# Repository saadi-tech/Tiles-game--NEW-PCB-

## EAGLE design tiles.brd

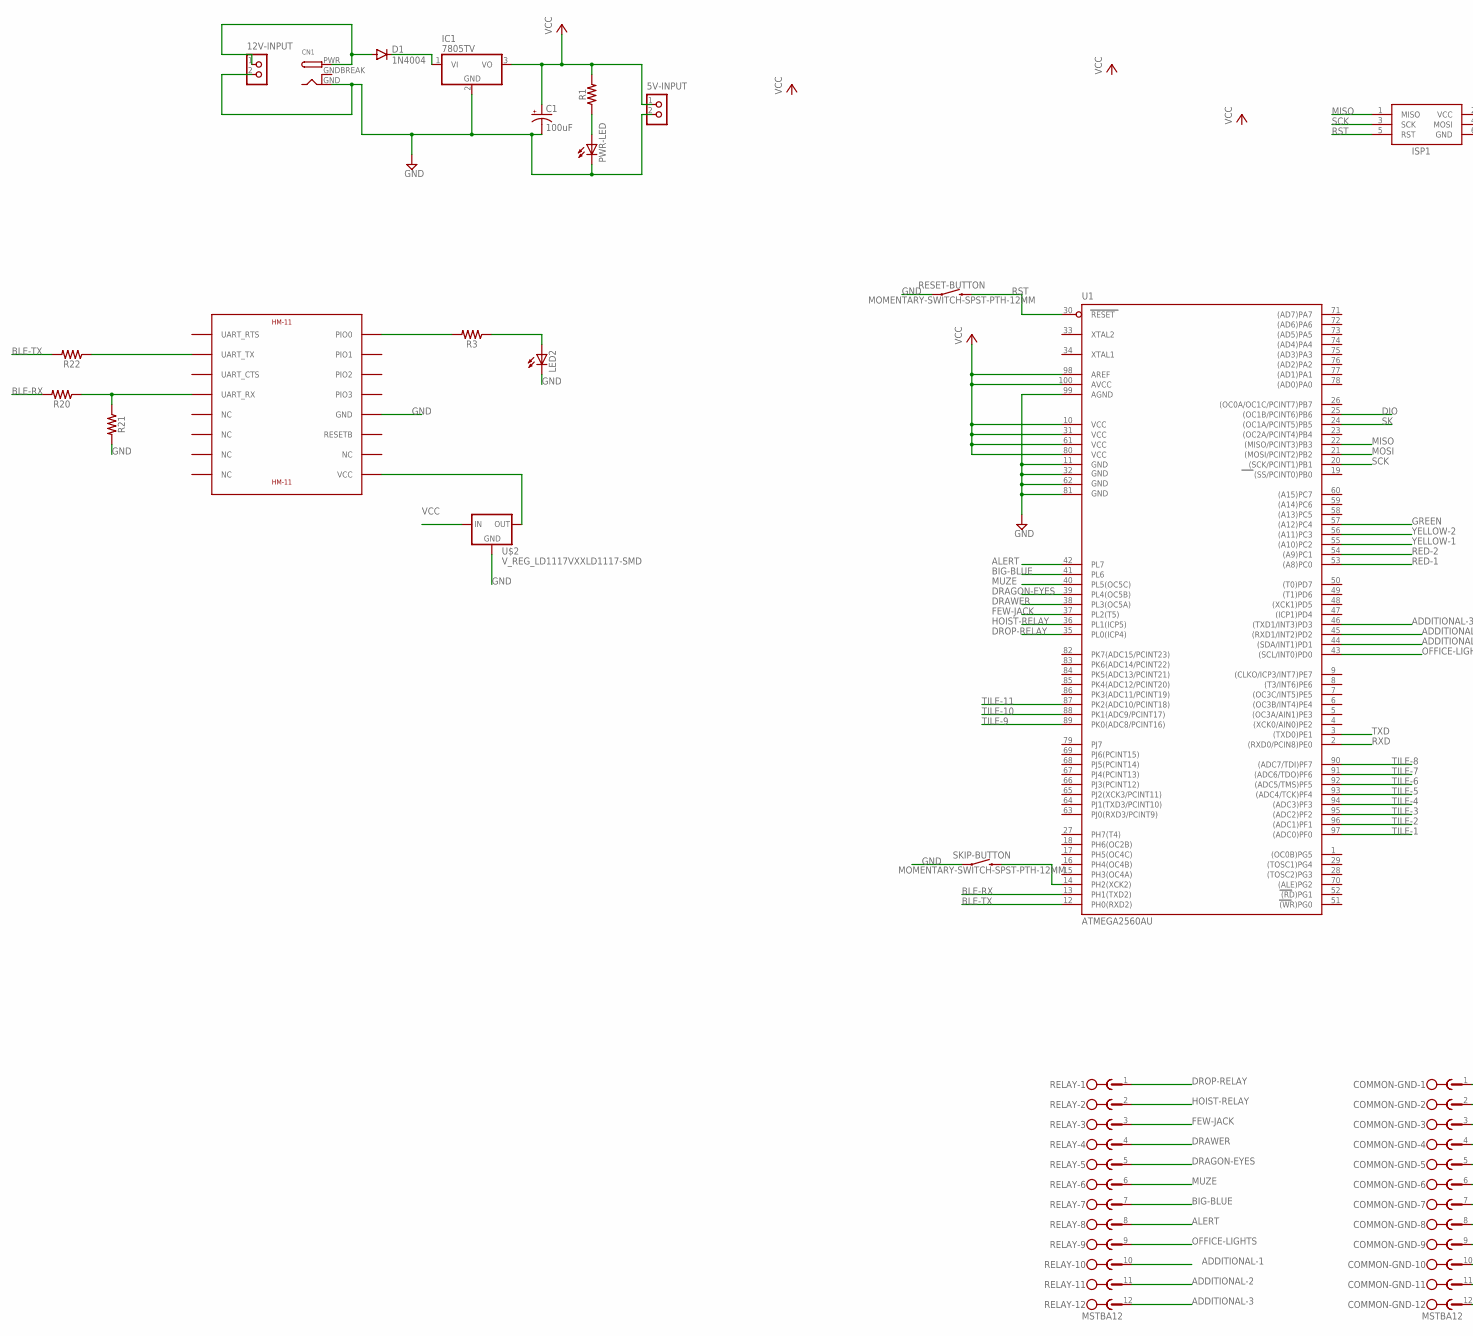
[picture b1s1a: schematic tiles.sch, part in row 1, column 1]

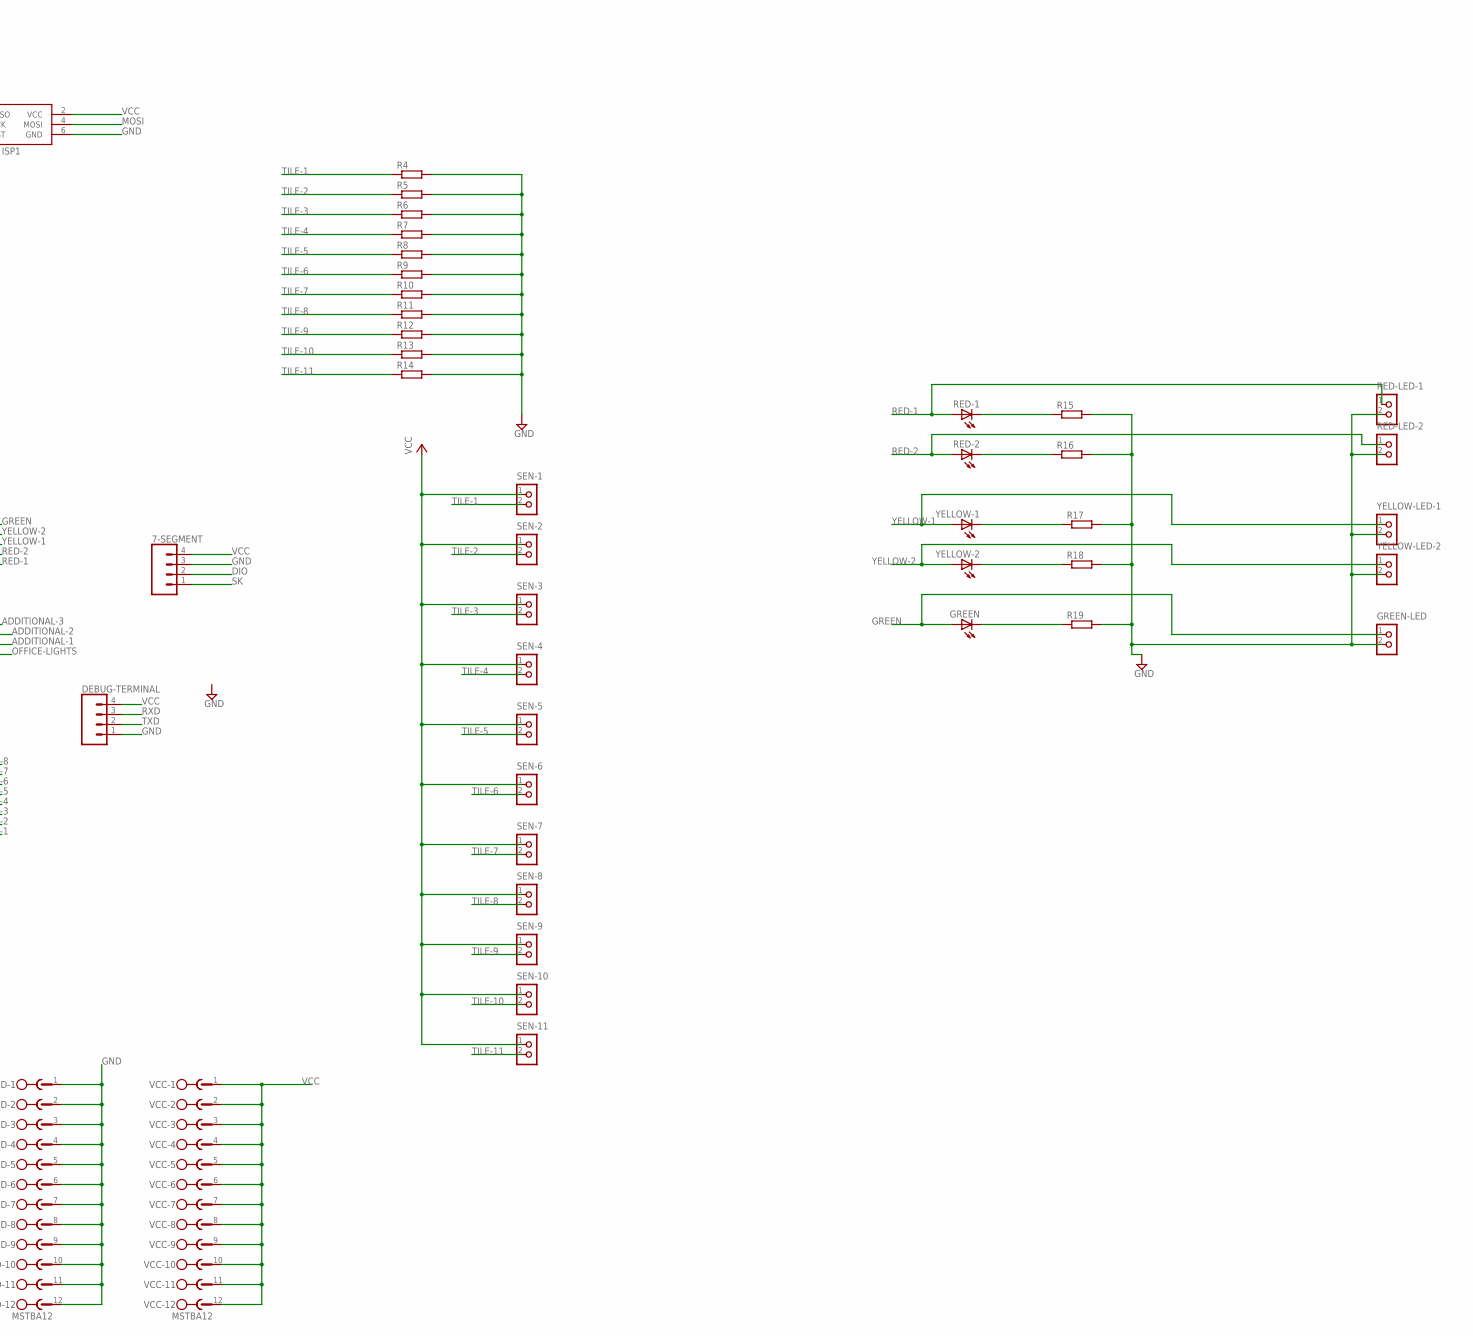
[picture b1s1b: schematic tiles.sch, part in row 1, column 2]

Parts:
5V-INPUT, 12V-INPUT: CON_TERMINAL_BLOCK_02-5MM; TERMINAL_BLOCK_2P_5
7-SEGMENT: CONN_04PTH; 1X04
C1: 100uF; CPOL-RADIAL-2.5MM-6.5MM
CN1: DCBARRELPTH; DCJACK_2MM_PTH
COMMON-GND: MSTBA12
D1: 1N4004; DO41-10
DEBUG-TERMINAL: CONN_04PTH; 1X04
GREEN: LED5MM
GREEN-LED: CON_TERMINAL_BLOCK_02-5MM; TERMINAL_BLOCK_2P_5
IC1: 7805TV; TO220V
ISP1: AVRISP-6; AVRISP
LED2: LED1206; LED-1206
PWR-LED: LED1206; LED-1206
R1, R3, R20, R21, R22: 1206
R4, R5, R6, R7, R8, R9, R10, R11, R12, R13, R14, R15, R16, R17, R18, R19: R-EU_0204/7; 0204/7
RED-1, RED-2: LED5MM
RED-LED-1, RED-LED-2: CON_TERMINAL_BLOCK_02-5MM; TERMINAL_BLOCK_2P_5
RELAY: MSTBA12
RESET-BUTTON: MOMENTARY-SWITCH-SPST-PTH-12MM; TACTILE_SWITCH_PTH_12MM
SEN-1, SEN-2, SEN-3, SEN-4, SEN-5, SEN-6, SEN-7, SEN-8, SEN-9, SEN-10, SEN-11: CON_TERMINAL_BLOCK_02-5MM; TERMINAL_BLOCK_2P_5
SKIP-BUTTON: MOMENTARY-SWITCH-SPST-PTH-12MM; TACTILE_SWITCH_PTH_12MM
U1: ATMEGA2560AU; TQFP100
U$1: HM-11
U$2: V_REG_LD1117VXXLD1117-SMD; SOT223
VCC: MSTBA12
YELLOW-1, YELLOW-2: LED5MM
YELLOW-LED-1, YELLOW-LED-2: CON_TERMINAL_BLOCK_02-5MM; TERMINAL_BLOCK_2P_5

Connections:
ADDITIONAL-1: RELAY.10, U1.44 ((SDA/INT1)PD1)
ADDITIONAL-2: RELAY.11, U1.45 ((RXD1/INT2)PD2)
ADDITIONAL-3: RELAY.12, U1.46 ((TXD1/INT3)PD3)
ALERT: RELAY.8, U1.42 (PL7)
BIG-BLUE: RELAY.7, U1.41 (PL6)
BLE-RX: R20.2, U1.13 (PH1(TXD2))
BLE-TX: R22.2, U1.12 (PH0(RXD2))
DIO: 7-SEGMENT.2, U1.25 ((OC1B/PCINT6)PB6)
DRAGON-EYES: RELAY.5, U1.39 (PL4(OC5B))
DRAWER: RELAY.4, U1.38 (PL3(OC5A))
DROP-RELAY: RELAY.1, U1.35 (PL0(ICP4))
FEW-JACK: RELAY.3, U1.37 (PL2(T5))
GND: 5V-INPUT.2, 7-SEGMENT.3, 12V-INPUT.2, C1.2 (-), CN1.GND, COMMON-GND.1, COMMON-GND.2, COMMON-GND.3, COMMON-GND.4, COMMON-GND.5, COMMON-GND.6, COMMON-GND.7, COMMON-GND.8, COMMON-GND.9, COMMON-GND.10, COMMON-GND.11, COMMON-GND.12, DEBUG-TERMINAL.1, GREEN-LED.2, IC1.2 (GND), ISP1.6 (GND), LED2.C, PWR-LED.C, R4.2, R5.2, R6.2, R7.2, R8.2, R9.2, R10.2, R11.2, R12.2, R13.2, R14.2, R15.2, R16.2, R17.2, R18.2, R19.2, R21.2, RED-LED-1.2, RED-LED-2.2, RESET-BUTTON.1, SKIP-BUTTON.1, U1.11 (GND), U1.32 (GND1), U1.62 (GND2), U1.81 (GND3), U1.99 (AGND), U$1.GND, U$2.1 (GND), YELLOW-LED-1.2, YELLOW-LED-2.2
GNDBREAK: CN1.GNDBREAK
GREEN: GREEN.A, GREEN-LED.1, U1.57 ((A12)PC4)
HOIST-RELAY: RELAY.2, U1.36 (PL1(ICP5))
MISO: ISP1.1 (MISO), U1.22 ((MISO/PCINT3)PB3)
MOSI: ISP1.4 (MOSI), U1.21 ((MOSI/PCINT2)PB2)
MUZE: RELAY.6, U1.40 (PL5(OC5C))
unnamed: 12V-INPUT.1, CN1.PWR, D1.A
unnamed: D1.C, IC1.1 (VI)
unnamed: R3.2, U$1.PIO0
unnamed: PWR-LED.A, R1.1
unnamed: R15.1, RED-1.K (C)
unnamed: R16.1, RED-2.K (C)
unnamed: R17.1, YELLOW-1.K (C)
unnamed: R18.1, YELLOW-2.K (C)
unnamed: GREEN.K (C), R19.1
unnamed: SKIP-BUTTON.3 (2), U1.14 (PH2(XCK2))
unnamed: LED2.A, R3.1
unnamed: U$1.VCC, U$2.2 (OUT)
unnamed: R20.1, R21.1, U$1.UART_RX
unnamed: R22.1, U$1.UART_TX
OFFICE-LIGHTS: RELAY.9, U1.43 ((SCL/INT0)PD0)
RED-1: RED-1.A, RED-LED-1.1, U1.53 ((A8)PC0)
RED-2: RED-2.A, RED-LED-2.1, U1.54 ((A9)PC1)
RST: ISP1.5 (RST), RESET-BUTTON.3 (2), U1.30 (RESET)
RXD: DEBUG-TERMINAL.3, U1.2 ((RXD0/PCIN8)PE0)
SCK: ISP1.3 (SCK), U1.20 ((SCK/PCINT1)PB1)
SK: 7-SEGMENT.1, U1.24 ((OC1A/PCINT5)PB5)
TILE-1: R4.1, SEN-1.2, U1.97 ((ADC0)PF0)
TILE-2: R5.1, SEN-2.2, U1.96 ((ADC1)PF1)
TILE-3: R6.1, SEN-3.2, U1.95 ((ADC2)PF2)
TILE-4: R7.1, SEN-4.2, U1.94 ((ADC3)PF3)
TILE-5: R8.1, SEN-5.2, U1.93 ((ADC4/TCK)PF4)
TILE-6: R9.1, SEN-6.2, U1.92 ((ADC5/TMS)PF5)
TILE-7: R10.1, SEN-7.2, U1.91 ((ADC6/TDO)PF6)
TILE-8: R11.1, SEN-8.2, U1.90 ((ADC7/TDI)PF7)
TILE-9: R12.1, SEN-9.2, U1.89 (PK0(ADC8/PCINT16))
TILE-10: R13.1, SEN-10.2, U1.88 (PK1(ADC9/PCINT17))
TILE-11: R14.1, SEN-11.2, U1.87 (PK2(ADC10/PCINT18))
TXD: DEBUG-TERMINAL.2, U1.3 ((TXD0)PE1)
VCC: 5V-INPUT.1, 7-SEGMENT.4, C1.1 (+), DEBUG-TERMINAL.4, IC1.3 (VO), ISP1.2 (VCC), R1.2, SEN-1.1, SEN-2.1, SEN-3.1, SEN-4.1, SEN-5.1, SEN-6.1, SEN-7.1, SEN-8.1, SEN-9.1, SEN-10.1, SEN-11.1, U1.10 (VCC), U1.31 (VCC1), U1.61 (VCC2), U1.80 (VCC3), U1.98 (AREF), U1.100 (AVCC), U$2.3 (IN), VCC.1, VCC.2, VCC.3, VCC.4, VCC.5, VCC.6, VCC.7, VCC.8, VCC.9, VCC.10, VCC.11, VCC.12
YELLOW-1: U1.55 ((A10)PC2), YELLOW-1.A, YELLOW-LED-1.1
YELLOW-2: U1.56 ((A11)PC3), YELLOW-2.A, YELLOW-LED-2.1

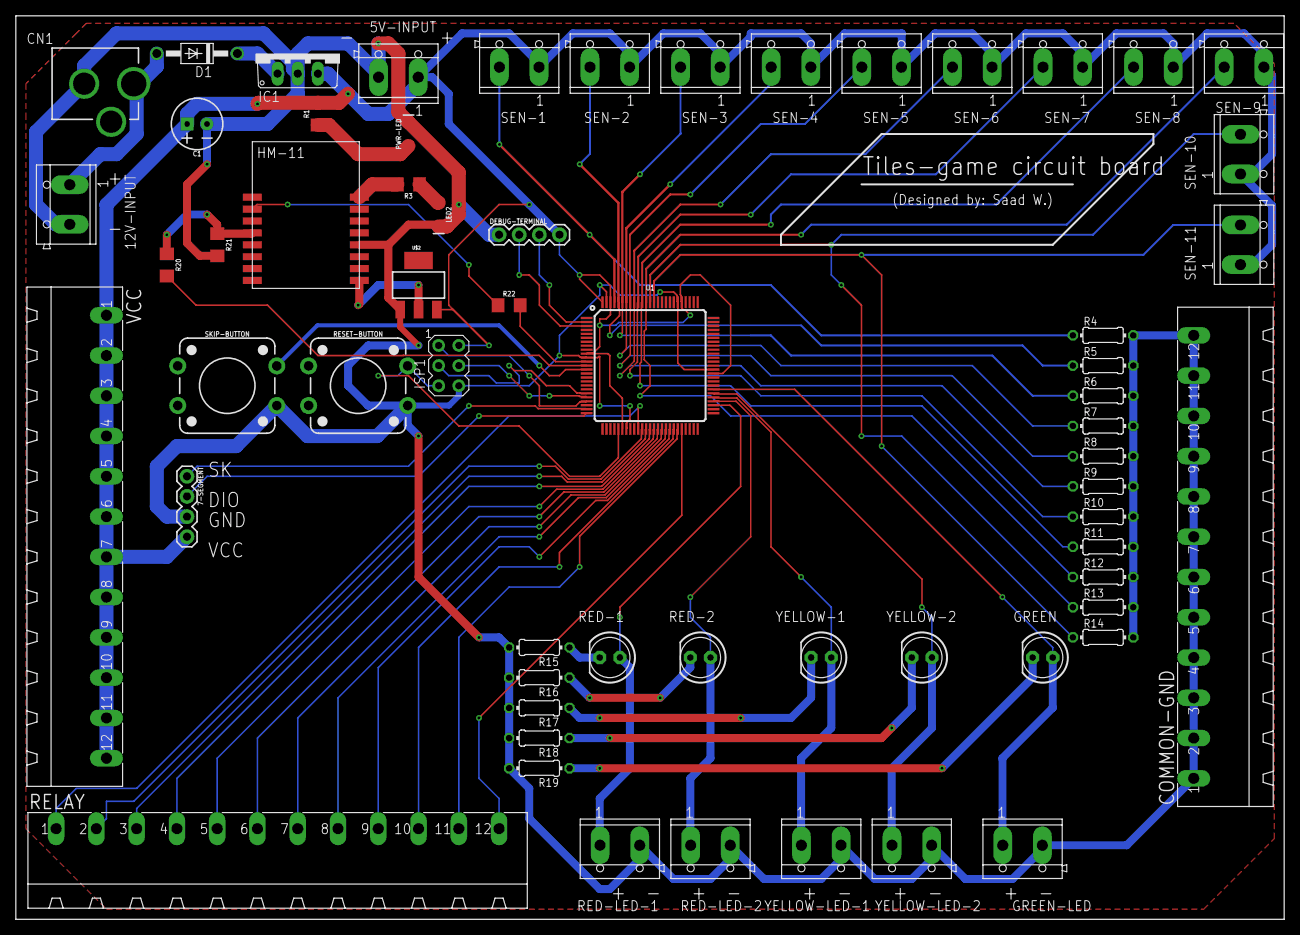
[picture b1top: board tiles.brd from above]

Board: 2 copper layers, 160.0 x 114.0 mm, 61 parts (0 on the bottom side), 54 nets.

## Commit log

2020-10-30 t from me
2020-10-30 oooooooooooooo

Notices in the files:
parts and their libraries:
SparkFun-Capacitors: Licensing: Creative Commons ShareAlike 4.0 International - https://creativecommons.org/licenses/by-sa/4.0
